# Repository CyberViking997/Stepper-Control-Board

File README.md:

# Stepper-Control-Board
A board that controls the motion of a stepper motor. With integrated driver and CANBus connection

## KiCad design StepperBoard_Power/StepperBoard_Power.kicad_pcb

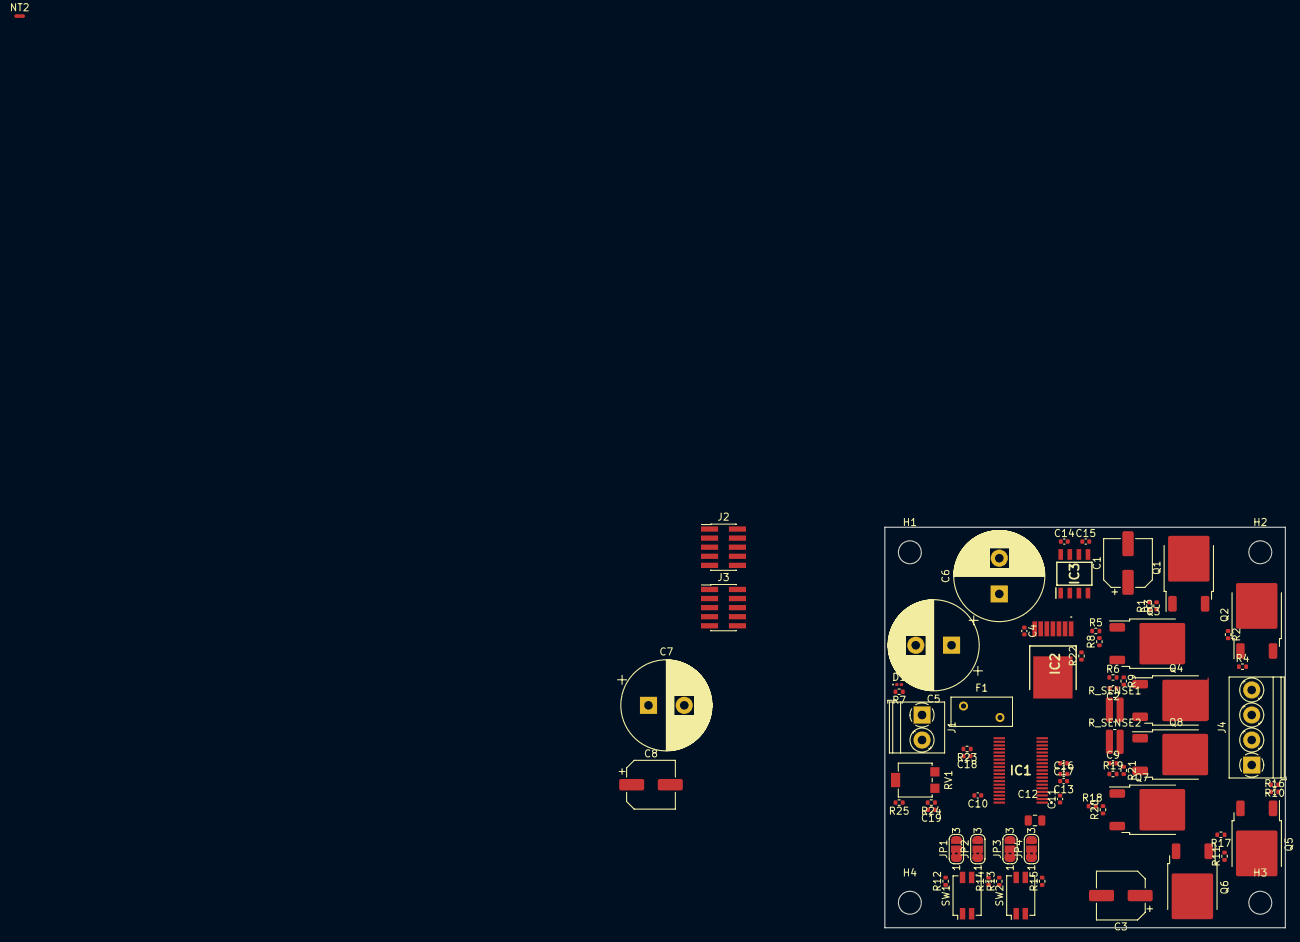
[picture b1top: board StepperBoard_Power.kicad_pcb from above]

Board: 2 copper layers, 56.0 x 56.0 mm, 76 parts (0 on the bottom side), 58 nets, no tracks yet.

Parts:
C1, C3, C8: 68u @ 50V; CP_Elec_6.3x7.7
C2, C4, C9, C18: 10n; C_0402_1005Metric
C5, C6, C7: 1000u @ 50V; CP_Radial_D12.5mm_P5.00mm
C10, C11, C16, C17, C19: 100u; C_0402_1005Metric
C12: 10u; C_0805_2012Metric
C13: 100n; C_0402_1005Metric
C14, C15: C; C_0402_1005Metric
D1: LED; LED_0201_0603Metric
F1: Fuse; Fuse_BelFuse_0ZRE0012FF_L8.3mm_W3.8mm
H1, H2, H3, H4: MountingHole; MountingHole_3.2mm_M3
IC1: A4989SLDTR-T; A3938SLDTRT
IC2: VN7007ALHTR; OCTAPAK
IC3: MCS1802GS-20-Z; SOIC127P600X175-8N
J1: Screw_Terminal_01x02; TerminalBlock_Phoenix_PT-1,5-2-3.5-H_1x02_P3.50mm_Horizontal
J2, J3: Conn_02x05_Odd_Even; PinHeader_2x05_P1.27mm_Vertical_SMD
J4: Screw_Terminal_01x04; TerminalBlock_Phoenix_PT-1,5-4-3.5-H_1x04_P3.50mm_Horizontal
JP1, JP2, JP3, JP4: SolderJumper_3_Bridged12; SolderJumper-3_P1.3mm_Bridged2Bar12_RoundedPad1.0x1.5mm_Num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
NT1: NetTie_2; NetTie-2_SMD_Pad0.2mm
NT2: NetTie_2; NetTie-2_SMD_Pad0.5mm
Q1, Q2, Q3, Q4, Q5, Q6, Q7, Q8: DMNH10H028SK3Q-13; TO-252-2 Tab1
R1, R2, R5, R6, R10, R11, R18, R19: 33; R_0402_1005Metric
R3, R4, R8, R9, R16, R17, R20, R21: 500k; R_0402_1005Metric
R7: 3.3k; R_0402_1005Metric
R12, R13, R14, R15, R23: 10k; R_0402_1005Metric
R22: 15k; R_0402_1005Metric
R24: 22k; R_0402_1005Metric
R25: 3k3; R_0402_1005Metric
RV1: 30k; Potentiometer_Bourns_3314G_Vertical
R_SENSE1, R_SENSE2: 0.05; R_0612_1632Metric
SW1, SW2: SW_DIP_x02; SW_DIP_SPSTx02_Slide_Copal_CHS-02A_W5.08mm_P1.27mm_JPin

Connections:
+3.3V: C14.1, C18.1, IC1.25 (VDD), IC3.8 (VCC), J2.1, J2.2, J3.1, J3.2, R12.1, R13.1, R14.1, R15.1, R24.2
+24V: C4.1, C5.1, C6.1, C7.1, C8.1, C13.2, F1.2, IC1.7 (VBB), IC2.8 (VCC), NT1.2
/+24V_Switch: IC2.1 (OUTPUT_1), IC2.2 (OUTPUT_2), IC2.3 (OUTPUT_3), IC3.1 (IP+_1), IC3.2 (IP+_2)
Bridge1_CA: C16.1, IC1.9 (S1A), J4.4, Q1.3 (S), Q3.1 (D), R3.1
Bridge1_CB: C17.1, IC1.14 (S1B), J4.3, Q2.3 (S), Q4.1 (D), R4.2
Bridge2_CA: C11.1, IC1.1 (C2A), J4.2, Q5.3 (S), Q7.1 (D), R16.1
Bridge2_CB: C10.1, IC1.36 (S2B), J4.1, Q6.3 (S), Q8.1 (D), R17.2
DIR: IC1.30 (DIR), J2.3
EN: IC1.19 (ENABLE), J2.5
GH1A: IC1.10 (GH1A), R1.1
GH1B: IC1.13 (GH1B), R2.1
GH2A: IC1.2 (GH2A), R10.1
GH2B: IC1.37 (GH2B), R11.1
GL1A: IC1.8 (GL1A), R5.1
GL1B: IC1.15 (GL1B), R6.1
GL2A: IC1.4 (GL2A), R18.1
GL2B: IC1.35 (GL2B), R19.1
GND: C1.2, C2.2, C3.2, C4.2, C5.2, C6.2, C7.2, C8.2, C9.2, J1.2, NT2.2, R_SENSE1.1, R_SENSE2.1
GNDD: C12.2, C13.1, C14.2, C15.2, C18.2, C19.2, IC1.20 (GND), IC2.7 (GND), IC3.5 (GND), J2.9, J2.10, J3.7, J3.8, J3.9, J3.10, NT2.1, R7.2, R23.2, R25.1, SW1.1, SW1.2, SW2.1, SW2.2
LSS1: C2.1, IC1.16 (LSS1), Q3.3 (S), Q4.3 (S), R8.1, R9.2, R_SENSE1.2
LSS2: C9.1, IC1.33 (LSS2), Q7.3 (S), Q8.3 (S), R20.1, R21.2, R_SENSE2.2
MS1: IC1.28 (MS1), JP1.2 (C)
MS1_uC: J3.6, JP1.3 (B)
MS2: IC1.29 (MS2), JP2.2 (C)
MS2_uC: J3.4, JP2.3 (B)
unnamed: D1.2 (A), NT1.1
unnamed: D1.1 (K), R7.1
unnamed: C16.2, IC1.11 (C1A)
unnamed: C17.2, IC1.12 (C1B)
unnamed: C10.2, IC1.38 (C2B)
unnamed: IC1.23 (OSC), R23.1
unnamed: C11.2, IC1.3 (S2A)
unnamed: C12.1, IC1.6 (VREG)
unnamed: IC2.4 (INPUT), R22.2
unnamed: C15.1, IC3.6 (FILT)
unnamed: JP1.1 (A), R12.2, SW1.4
unnamed: JP2.1 (A), R14.2, SW1.3
unnamed: JP3.1 (A), R13.2, SW2.4
unnamed: JP4.1 (A), R15.2, SW2.3
unnamed: Q1.2 (G), R1.2, R3.2
unnamed: Q2.2 (G), R2.2, R4.1
unnamed: Q3.2 (G), R5.2, R8.2
unnamed: Q4.2 (G), R6.2, R9.1
unnamed: Q5.2 (G), R10.2, R16.2
unnamed: Q6.2 (G), R11.2, R17.1
unnamed: Q7.2 (G), R18.2, R20.2
unnamed: Q8.2 (G), R19.2, R21.1
unnamed: R25.2, RV1.2, RV1.3
PFD1: IC1.31 (PFD1), JP3.2 (C)
PFD1_uC: J3.3, JP3.3 (B)
PFD2: IC1.27 (PFD2), JP4.2 (C)
PFD2_uC: J3.5, JP4.3 (B)
RST: IC1.22 (RESET), J2.6
Sense_uC: IC3.7 (VOUT), J2.8
Switch_uC: J2.7, R22.1
VCC: F1.1, J1.1
VDDF: C1.1, C3.1, IC3.3 (IP-_1), IC3.4 (IP-_2), Q1.1 (D), Q2.1 (D), Q5.1 (D), Q6.1 (D)
VRef: C19.1, IC1.21 (REF), R24.1, RV1.1

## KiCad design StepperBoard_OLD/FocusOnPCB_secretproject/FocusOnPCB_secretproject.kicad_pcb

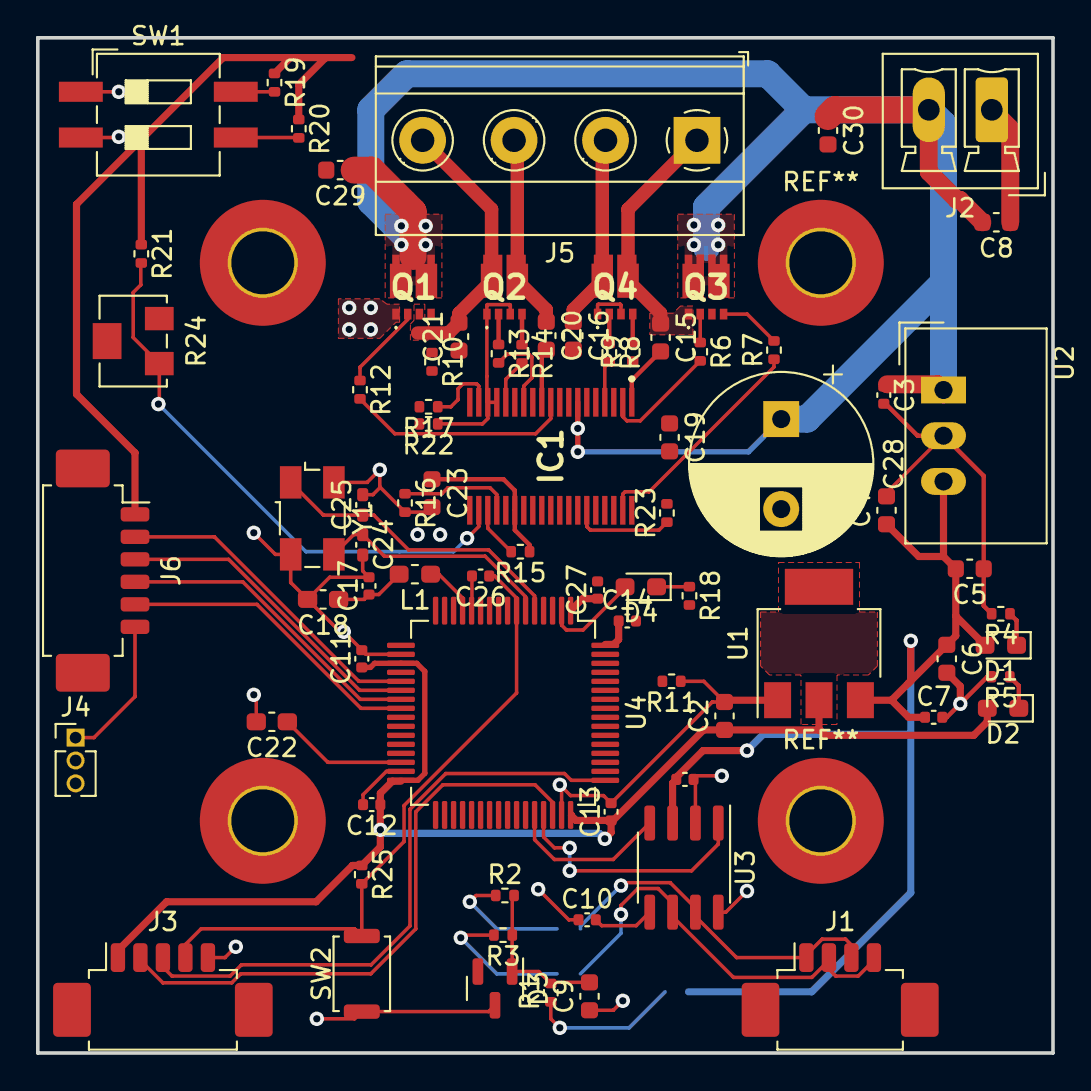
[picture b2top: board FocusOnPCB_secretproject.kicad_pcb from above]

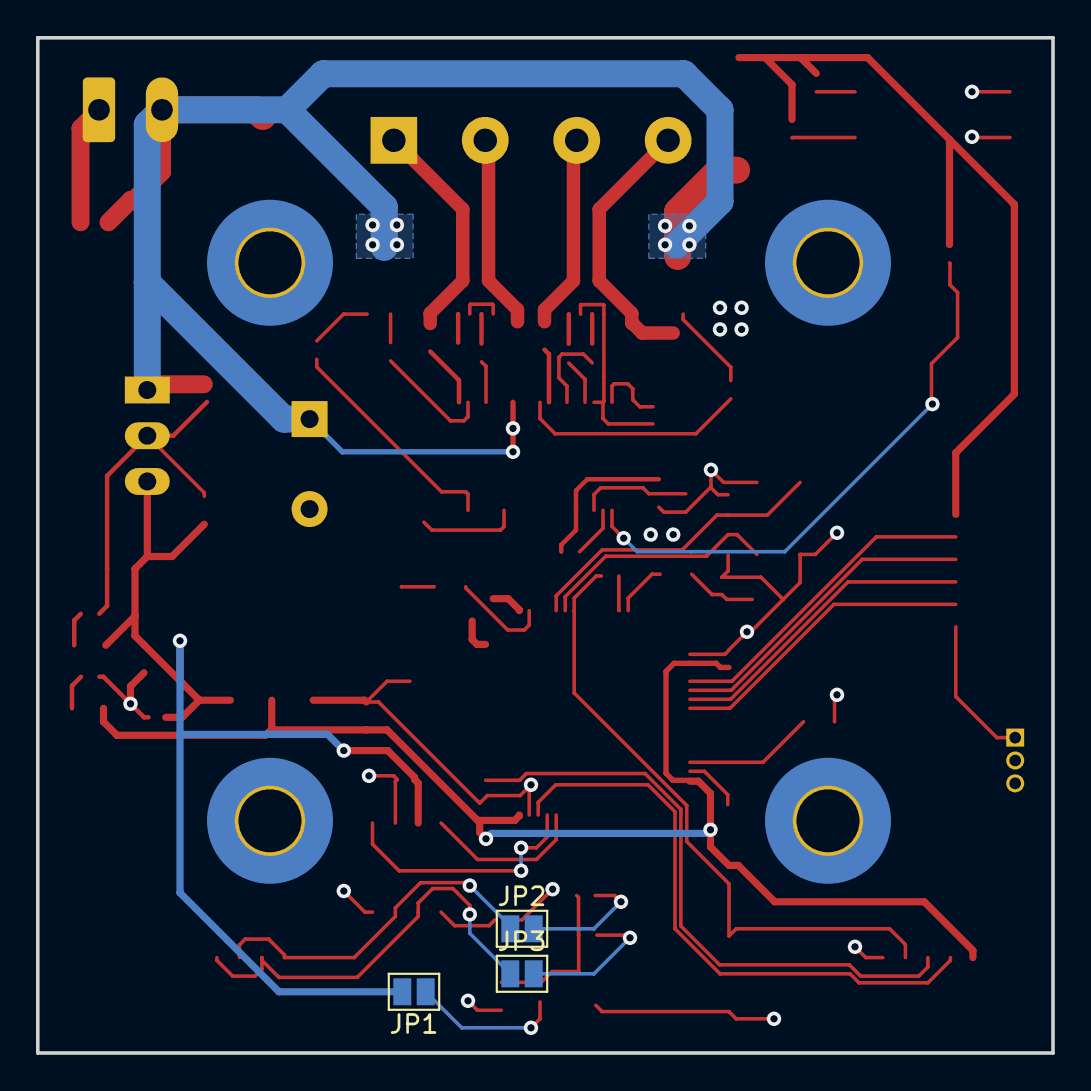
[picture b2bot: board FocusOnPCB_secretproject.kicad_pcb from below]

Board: 4 copper layers, 56.4 x 56.4 mm, 81 parts (3 on the bottom side), 66 nets.

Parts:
C1, C3, C7, C10, C26: 100n; C_0402_1005Metric
C2, C4, C6, C29, C30: 10u; C_0603_1608Metric
C5: 22u; C_0603_1608Metric
C8: 10u@50V; C_0603_1608Metric
C9: 4.7n; C_0603_1608Metric
C11, C12, C13, C14, C27: 100nF; C_0402_1005Metric
C15, C16, C19, C20, C21, C23: C; C_0603_1608Metric
C17: 10nF; C_0402_1005Metric
C18: 1uF; C_0603_1608Metric_Pad1.08x0.95mm_HandSolder
C22: 4.7uF; C_0603_1608Metric_Pad1.08x0.95mm_HandSolder
C24, C25: 18p; C_0402_1005Metric_Pad0.74x0.62mm_HandSolder
C28: C_Polarized; CP_Radial_D10.0mm_P5.00mm
D1, D2, D4: LED; LED_0603_1608Metric_Pad1.05x0.95mm_HandSolder
D3: MMBZxx; SOT-23
IC1: A4989SLDTR-T; A3938SLDTRT
J1: Screw_Terminal_01x04; Molex_PicoBlade_53261-0471_1x04-1MP_P1.25mm_Horizontal
J2: Conn_01x02; PhoenixContact_MCV_1,5_2-G-3.5_1x02_P3.50mm_Vertical
J3: SWD; Molex_PicoBlade_53261-0571_1x05-1MP_P1.25mm_Horizontal
J4: UART; PinHeader_1x03_P1.27mm_Vertical
J5: Screw_Terminal_01x04; TerminalBlock_Phoenix_MKDS-1,5-4-5.08_1x04_P5.08mm_Horizont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
J6: Conn_01x06; Molex_PicoBlade_53261-0671_1x06-1MP_P1.25mm_Horizontal
JP1, JP2, JP3: SolderJumper_2_Open; SolderJumper-2_P1.3mm_Open_Pad1.0x1.5mm
L1: L; L_0603_1608Metric_Pad1.05x0.95mm_HandSolder
Q1, Q2, Q3, Q4: DMT3020LDV-7; DMT3020LDV7
R1, R2, R3, R4, R5, R6, R7, R8, R9, R10, R12, R13, R14, R15, R16, R17, R18, R19, R20, R21, R22, R23: R; R_0402_1005Metric
R11: 0Ohm; R_0402_1005Metric
R24: R_Variable; Potentiometer_Bourns_3214W_Vertical
R25: 10k; R_0402_1005Metric
SW1: SW_DIP_x02; SW_DIP_SPSTx02_Slide_6.7x6.64mm_W8.61mm_P2.54mm_LowProfile
SW2: SW_Push; SW_Push_SPST_NO_Alps_SKRK
U1: AMS1117-3.3; SOT-223-3_TabPin2
U2: TSR_1-2450; Converter_DCDC_TRACO_TSR-1_THT
U3: MCP2562-E-SN; SOIC-8_3.9x4.9mm_P1.27mm
U4: STM32F446RETx; LQFP-64_10x10mm_P0.5mm
Y1: ABM3B-8.000MHZ-B2-T; Crystal_SMD_Abracon_ABM3B-4Pin_5.0x3.2mm

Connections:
+3.3V: C10.2, U3.5 (Vio)
+3V3: C2.1, C11.1, C12.1, C13.1, C14.1, C27.1, D2.2 (A), J3.1, R25.1, U1.2 (VO), U4.1 (VBAT), U4.19 (VDD), U4.32 (VDD), U4.48 (VDD), U4.64 (VDD)
+5V: C1.2, C4.1, C5.2, C6.1, C7.1, C23.1, D1.2 (A), IC1.25 (VDD), J6.1, JP1.2 (B), R15.1, R19.1, R20.1, R21.1, U1.3 (VI), U2.3 (Vout), U3.3 (VDD)
+24V: C3.1, C8.2, C28.1, C29.1, C30.1, IC1.7 (VBB), J2.2, Q1.5 (D2_1), Q1.6 (D2_2), Q1.7 (D1_1), Q1.8 (D1_2), Q1.9 (D1_3), Q1.10 (D2_3), Q3.5 (D2_1), Q3.6 (D2_2), Q3.7 (D1_1), Q3.8 (D1_2), Q3.9 (D1_3), Q3.10 (D2_3), U2.1 (Vin)
CAN+: J1.1, J1.3, JP2.1 (A), U3.7 (CANH)
CAN-: J1.2, J1.4, JP3.1 (A), U3.6 (CANL)
GND: C1.1, C2.2, C3.2, C4.2, C5.1, C6.2, C7.2, C8.1, C9.1, C10.1, C11.2, C12.2, C13.2, C14.2, C17.2, C18.2, C19.2, C22.2, C23.2, C24.2, C25.2, C26.2, C27.2, C28.2, C29.2, C30.2, D3.3 (A), IC1.20 (GND), IC1.27 (PFD2), IC1.31 (PFD1), J2.1, J3.5, J4.1, J6.6, R4.2, R5.2, R11.1, R16.2, R17.2, R18.2, R22.2, R23.2, R24.2, SW1.1, SW1.2, SW2.1, U1.1 (GND), U2.2 (GND), U3.2 (VSS), U3.8 (STBY), U4.12 (VSSA), U4.18 (VSS), U4.31 (VSS), U4.47 (VSS), U4.63 (VSS), Y1.2 (GND_1), Y1.4 (GND_2)
Gate1_1: Q1.2 (G1), R12.1
Gate1_2: Q1.4 (G2), R10.1
Gate2_1: Q2.2 (G1), R13.1
Gate2_2: Q2.4 (G2), R14.1
Gate3_1: Q3.2 (G1), R6.1
Gate3_2: Q3.4 (G2), R7.2
Gate4_1: Q4.2 (G1), R8.1
Gate4_2: Q4.4 (G2), R9.2
MS1: IC1.28 (MS1), R19.2, SW1.4
MS2: IC1.29 (MS2), R20.2, SW1.3
NRST: C26.1, J3.4, R25.2, SW2.2, U4.7 (NRST)
unnamed: C9.2, D3.1 (K), R1.2, R2.2, R3.1
unnamed: C17.1, C18.1, L1.2
unnamed: D1.1 (K), R4.1
unnamed: D2.1 (K), R5.1
unnamed: D4.1 (K), R18.1
unnamed: C20.2, IC1.11 (C1A)
unnamed: C21.1, IC1.12 (C1B)
unnamed: C15.2, IC1.1 (C2A)
unnamed: C16.2, IC1.38 (C2B)
unnamed: IC1.10 (GH1A), R12.2
unnamed: IC1.13 (GH1B), R13.2
unnamed: IC1.2 (GH2A), R6.2
unnamed: IC1.37 (GH2B), R7.1
unnamed: IC1.8 (GL1A), R10.2
unnamed: IC1.15 (GL1B), R14.2
unnamed: IC1.4 (GL2A), R8.2
unnamed: IC1.35 (GL2B), R9.1
unnamed: IC1.23 (OSC), R16.1
unnamed: IC1.22 (RESET), R15.2
unnamed: IC1.18 (SR), R17.1
unnamed: C19.1, IC1.6 (VREG)
unnamed: JP1.1 (A), R1.1
unnamed: JP2.2 (B), R2.1
unnamed: JP3.2 (B), R3.2
unnamed: R11.2, U4.60 (BOOT0)
unnamed: C22.1, U4.30 (VCAP_1)
unnamed: L1.1, U4.13 (VDDA)
OSC_N: C25.1, U4.5 (PH0), Y1.1 (NC_1)
OSC_P: C24.1, U4.6 (PH1), Y1.3 (NC_2)
PA5\SPI1_SCK: J6.2, U4.21 (PA5)
PA6\SPI1_MISO: J6.3, U4.22 (PA6)
PA7\SPI1_MOSI: J6.4, U4.23 (PA7)
PA11\CAN1RX: U3.4 (RXD), U4.44 (PA11)
PA12\CAN1TX: U3.1 (TXD), U4.45 (PA12)
PA13\SWDIO: J3.2, U4.46 (PA13)
PA14\SWCLK: J3.3, U4.49 (PA14)
PB15\Stp_EN: IC1.19 (ENABLE), U4.36 (PB15)
PC4\SPI1_CS: J6.5, U4.24 (PC4)
PC6\STEP: IC1.26 (STEP), U4.37 (PC6)
PC7\DIR: IC1.30 (DIR), U4.38 (PC7)
PC13: D4.2 (A), U4.2 (PC13)
Sense1: IC1.16 (LSS1), IC1.17 (SENSE1), Q2.1 (S1), Q2.3 (S2), R22.1
Sense2: IC1.32 (SENSE2), IC1.33 (LSS2), Q4.1 (S1), Q4.3 (S2), R23.1
Vref: IC1.21 (REF), R21.2, R24.1
W1_1: C20.1, IC1.9 (S1A), J5.3, Q1.1 (S1), Q2.5 (D2_1), Q2.6 (D2_2), Q2.10 (D2_3)
W1_2: C21.2, IC1.14 (S1B), J5.4, Q1.3 (S2), Q2.7 (D1_1), Q2.8 (D1_2), Q2.9 (D1_3)
W2_1: C15.1, IC1.3 (S2A), J5.1, Q3.1 (S1), Q4.5 (D2_1), Q4.6 (D2_2), Q4.10 (D2_3)
W2_2: C16.1, IC1.36 (S2B), J5.2, Q3.3 (S2), Q4.7 (D1_1), Q4.8 (D1_2), Q4.9 (D1_3)

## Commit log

2023-11-21 First project upload
2023-12-15 Updated version on GitHub
2023-12-15 Added NetTies and NetClasses
    Added the NetTies library in CommonComponents folder and defined some NetClasses.
    Also fixed the position of some components.
